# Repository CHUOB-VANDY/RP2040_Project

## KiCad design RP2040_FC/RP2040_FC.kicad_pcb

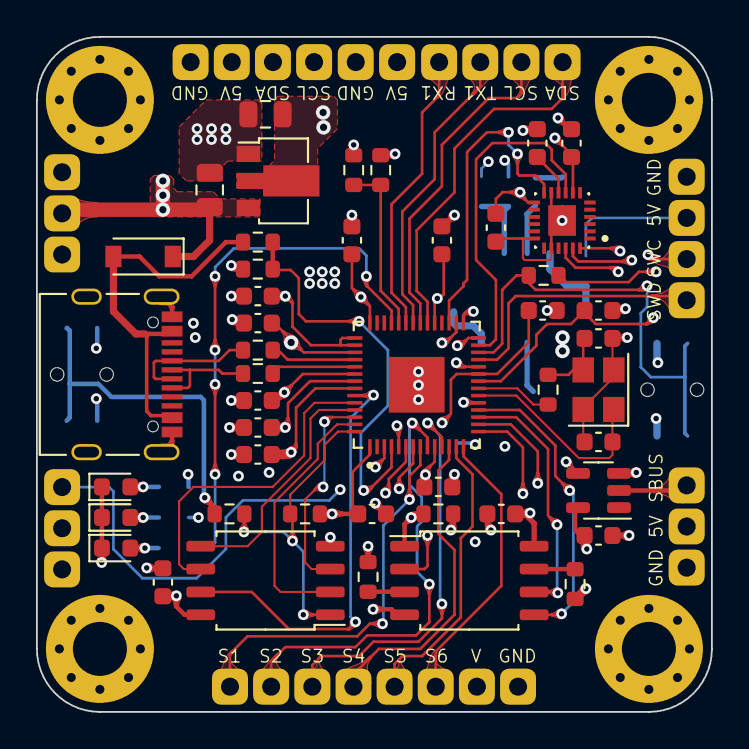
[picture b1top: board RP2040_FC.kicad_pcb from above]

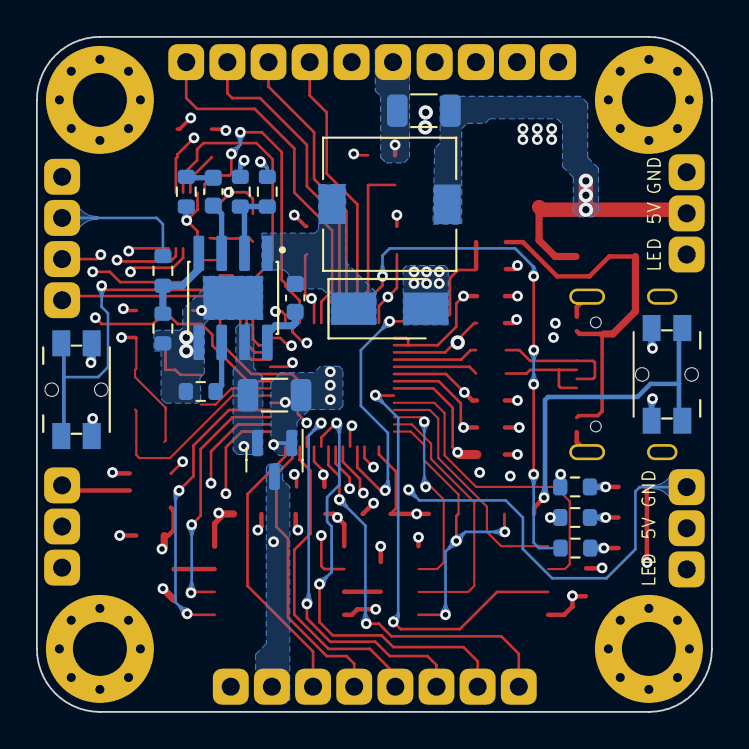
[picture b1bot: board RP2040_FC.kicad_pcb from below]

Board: 4 copper layers, 37.5 x 37.5 mm, 76 parts (19 on the bottom side), 64 nets.

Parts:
C1, C2: 20pF; C_0603_1608Metric
C3, C6: 1uF; C_0603_1608Metric
C4, C5, C7, C8, C9, C10, C11, C12, C13, C14, C15, C17, C18, C19, C23: 100nF; C_0603_1608Metric
C16: 10nF; C_0603_1608Metric
C20: 10uF; C_1206_3216Metric
C21: 150pF; C_0603_1608Metric
C22: 22uF; C_1206_3216Metric
C24, C25: 10uF; C_0805_2012Metric
D1: SS34; D_SMA
D2: B5819; D_SOD-123
D3: LEDB; LED_0603_1608Metric
D4: LEDG; LED_0603_1608Metric
D5: LEDR; LED_0603_1608Metric
H1, H2, H3, H4: MountingHole; MountingHole_3mm_Pad_Via
J1: SBUS; pad_01x03
J2: USB_C; USB_C_Receptacle_Palconn_UTC16-G
J3: PWM; pad_01x08
J4: GPS; pad_01x06
J5: I2C; pad_01x04
J6: DEBUG; pad_01x04
J7, J8: LED_STRIP; pad_01x03
L1: 22uF; L_7.3x7.3_H4.5
Q1: AO3401A; SOT-23
R1, R5, R8, R9, R10, R11, R18: 10k; R_0603_1608Metric
R2, R3, R19: 1k; R_0603_1608Metric
R4: DNP; R_0603_1608Metric
R6, R7: 27R; R_0603_1608Metric
R12, R14, R15: 100k; R_0603_1608Metric
R13: 24k; R_0603_1608Metric
R16: 210k; R_0603_1608Metric
R17: 40.2k; R_0603_1608Metric
R20: 330R; R_0603_1608Metric
R21: 220R; R_0603_1608Metric
R22: 270R; R_0603_1608Metric
SW1: RESET; Panasonic_EVQPUM_EVQPUD
SW2: BOOT; Panasonic_EVQPUM_EVQPUD
U1: RP2040; QFN40P700X700X90-57N
U2, U5: W25Q32JVSS; SOIC-8_5.23x5.23mm_P1.27mm
U3: MPU-6500; QFN40P300X300X95-25N
U4: SN74ACH1G04; SOT-23-5
U6: MP1584EN; SOIC127P600X170-9N
U7: AZ1117-3.3; SOT-89-3
Y1: 12MHz; Crystal_SMD_3225-4Pin_3.2x2.5mm

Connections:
+1V1: C3.1, C4.1, C5.1, U1.23 (DVDD), U1.45 (VREG_VOUT), U1.50 (DVDD)
+3V3: C6.1, C7.1, C8.1, C9.1, C10.1, C11.1, C12.1, C13.1, C14.2, C16.1, C17.1, C18.1, C19.1, C25.1, R1.2, R4.2, R9.1, R10.1, R11.1, R21.1, U1.1 (IOVDD), U1.10 (IOVDD), U1.22 (IOVDD), U1.33 (IOVDD), U1.42 (IOVDD), U1.43 (ADC_AVDD), U1.44 (VREG_VIN), U1.48 (USB_VDD), U1.49 (IOVDD), U2.8 (VCC), U3.8 (VDDIO), U3.13 (VDD), U4.5 (VDD), U5.8 (VCC), U7.2 (VO)
+5V: C22.1, C24.1, D2.1 (K), J1.2, J4.5, J5.3, J6.3, J7.2, J8.2, L1.2, R16.1, R20.1, U7.3 (VI)
/BOOT: R3.1, SW2.1
/BST: C23.1, U6.8 (BST)
/COMP: C21.1, U6.3 (COMP)
/D+: J2.A6 (D+), J2.B6 (D+), R7.1
/D-: J2.A7 (D-), J2.B7 (D-), R6.1
/EN: R12.2, R13.1, U6.2 (EN)
/FB: R16.2, R17.1, U6.4 (FB)
/FREQ: R14.1, U6.6 (FREQ)
/GYR0_INT: U1.31 (GPIO20), U3.12 (INT)
/I2C0_SCL: J5.1, U1.7 (GPIO5)
/I2C0_SDA: J5.2, U1.6 (GPIO4)
/I2C1_SCL: J4.2, U1.35 (GPIO23)
/I2C1_SDA: J4.1, U1.34 (GPIO22)
/IO2: R10.2, U5.3 (IO2)
/IO3: R11.2, U5.7 (IO3)
/LED: R22.1, U1.39 (GPIO27/ADC1)
/LED_STRIP: J7.1, J8.1, U1.5 (GPIO3)
/QSPI_CSN: R3.2, R4.1, U1.56 (QSPI_CSN), U2.1 (~CS)
/QSPI_SCLK: U1.52 (QSPI_SCLK), U2.6 (CLK)
/QSPI_SD0: U1.53 (QSPI_SD0), U2.5 (DI(IO0))
/QSPI_SD1: U1.55 (QSPI_SD1), U2.2 (DO(IO1))
/QSPI_SD2: U1.54 (QSPI_SD2), U2.3 (IO2)
/QSPI_SD3: U1.51 (QSPI_SD3), U2.7 (IO3)
/REGOUT: C15.1, U3.10 (REGOUT)
/RUN: R1.1, SW1.1, U1.26 (RUN)
/RX0: U1.3 (GPIO1), U4.4 (Y)
/RX1: J4.4, U1.37 (GPIO25)
/S1: J3.1, U1.8 (GPIO6)
/S2: J3.2, U1.9 (GPIO7)
/S3: J3.3, U1.11 (GPIO8)
/S4: J3.4, U1.12 (GPIO9)
/S5: J3.5, U1.13 (GPIO10)
/S6: J3.6, U1.14 (GPIO11)
/SBUS: J1.3, U4.2 (A)
/SPI0_CLK: U1.29 (GPIO18), U3.23 (SCL/SCLK)
/SPI0_CSN: U1.28 (GPIO17), U3.22 (NCS)
/SPI0_MISO: U1.27 (GPIO16), U3.9 (AD0/SDO)
/SPI0_MOSI: U1.30 (GPIO19), U3.24 (SDA/SDI)
/SPI1_CSN: R9.2, U1.16 (GPIO13), U5.1 (~CS)
/SPI1_MISO: U1.15 (GPIO12), U5.2 (DO(IO1))
/SPI1_MOSI: U1.18 (GPIO15), U5.5 (DI(IO0))
/SPI1_SCK: U1.17 (GPIO14), U5.6 (CLK)
/SW: C23.2, D1.1 (K), L1.1, U6.1 (SW)
/SWC: J6.2, U1.24 (SWCLK)
/SWD: J6.1, U1.25 (SWD)
/TX1: J4.3, U1.36 (GPIO24)
/USB_D+: R7.2, U1.47 (USB_DP)
/USB_DETECT: R5.1, R8.2, U1.4 (GPIO2)
/USB_D_: R6.2, U1.46 (USB_DM)
/V: J3.7, Q1.3 (D), R18.1
/VIN: C20.1, Q1.2 (S), R12.1, U6.7 (VIN)
/VOL: R18.2, R19.1, U1.38 (GPIO26/ADC0)
/XIN: C1.1, U1.20 (XIN), Y1.1
/XOUT: R2.2, U1.21 (XOUT)
GND: C1.2, C2.2, C3.2, C4.2, C5.2, C6.2, C7.2, C8.2, C9.2, C10.2, C11.2, C12.2, C13.2, C14.1, C15.2, C16.2, C17.2, C18.2, C19.2, C20.2, C22.2, C24.2, C25.2, D1.2 (A), D3.1 (K), D4.1 (K), D5.1 (K), J1.1, J2.A1 (GND), J2.A12 (GND), J2.B1 (GND), J2.B12 (GND), J2.S1 (SHIELD), J3.8, J4.6, J5.4, J6.4, J7.3, J8.3, Q1.1 (G), R8.1, R13.2, R14.2, R15.2, R17.2, R19.2, SW1.2, SW2.2, U1.19 (TESTEN), U1.57 (GND), U2.4 (GND), U3.11 (FSYNC), U3.18 (GND), U3.20 (RESV_2), U3.25 (EXP), U4.3 (GND), U5.4 (GND), U6.5 (GND), U6.9 (GND), U7.1 (GND), Y1.2, Y1.4
unnamed: C2.1, R2.1, Y1.3
unnamed: C21.2, R15.1
unnamed: D3.2 (A), R20.2
unnamed: D4.2 (A), R21.2
unnamed: D5.2 (A), R22.2
VBUS: D2.2 (A), J2.A4 (VBUS), J2.A9 (VBUS), J2.B4 (VBUS), J2.B9 (VBUS), R5.2

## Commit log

2022-10-29 add kicad folder
